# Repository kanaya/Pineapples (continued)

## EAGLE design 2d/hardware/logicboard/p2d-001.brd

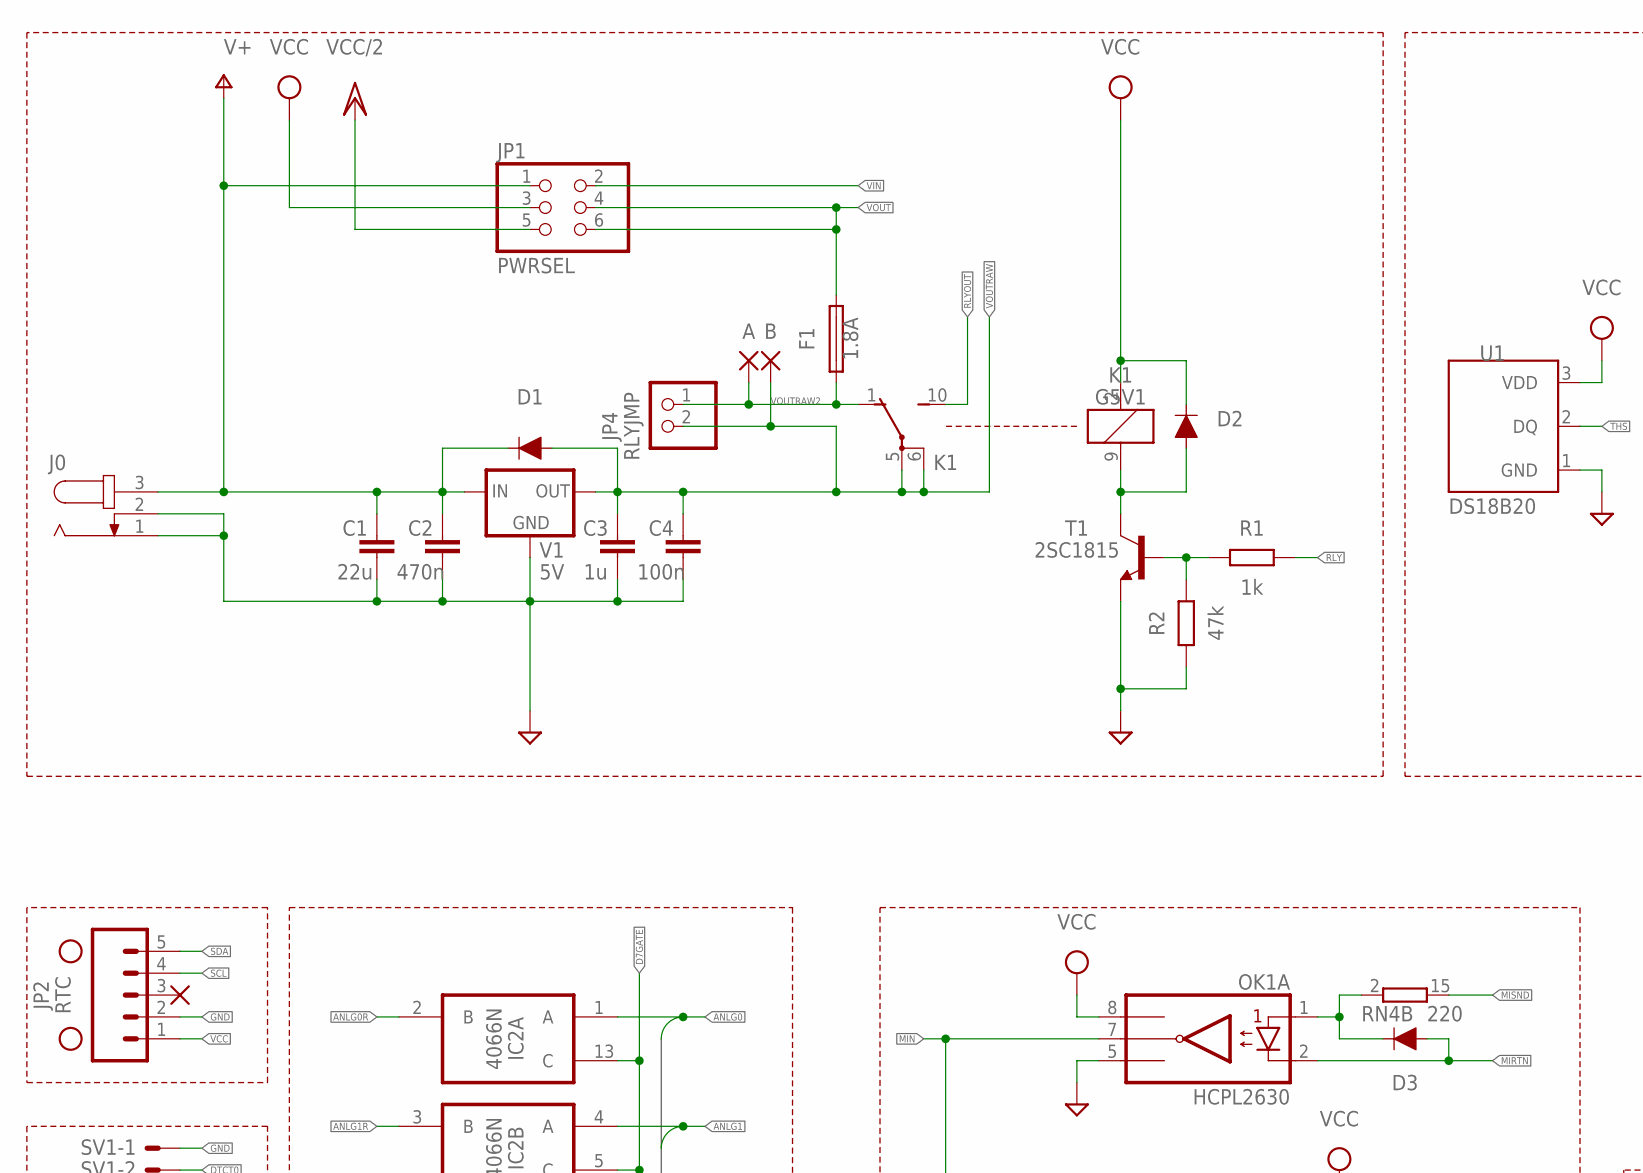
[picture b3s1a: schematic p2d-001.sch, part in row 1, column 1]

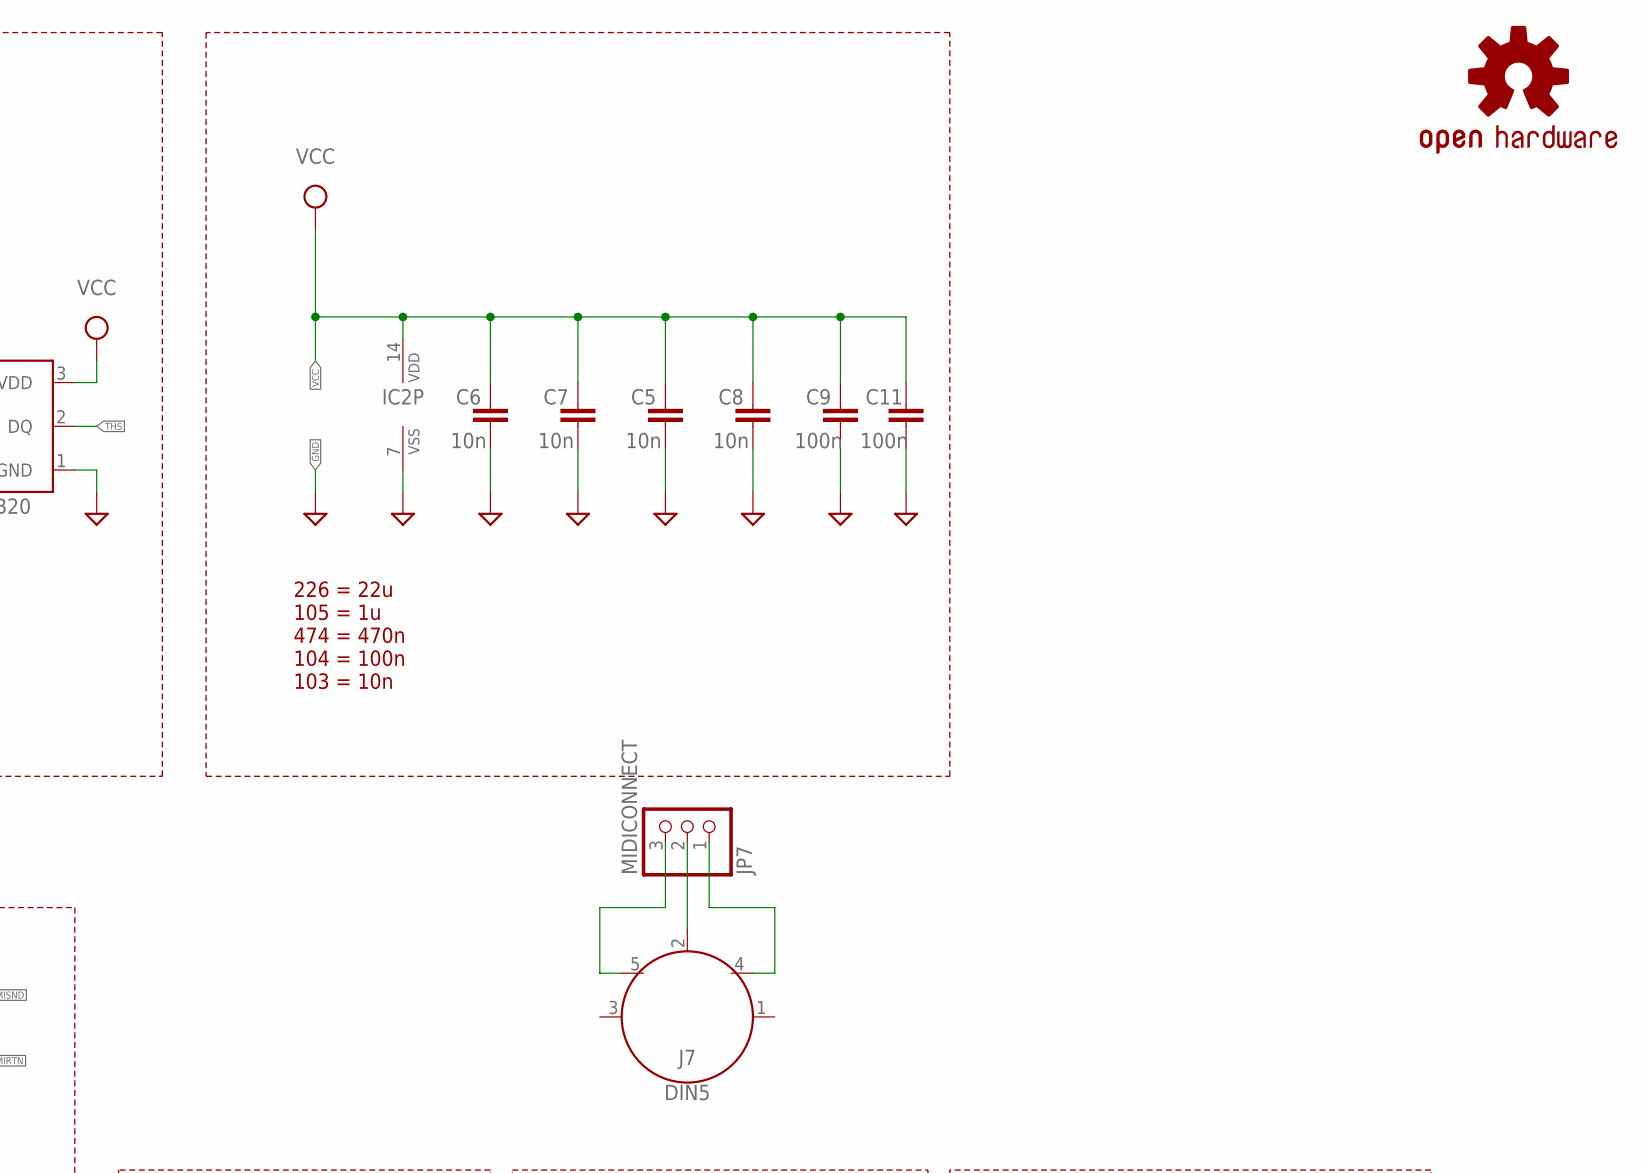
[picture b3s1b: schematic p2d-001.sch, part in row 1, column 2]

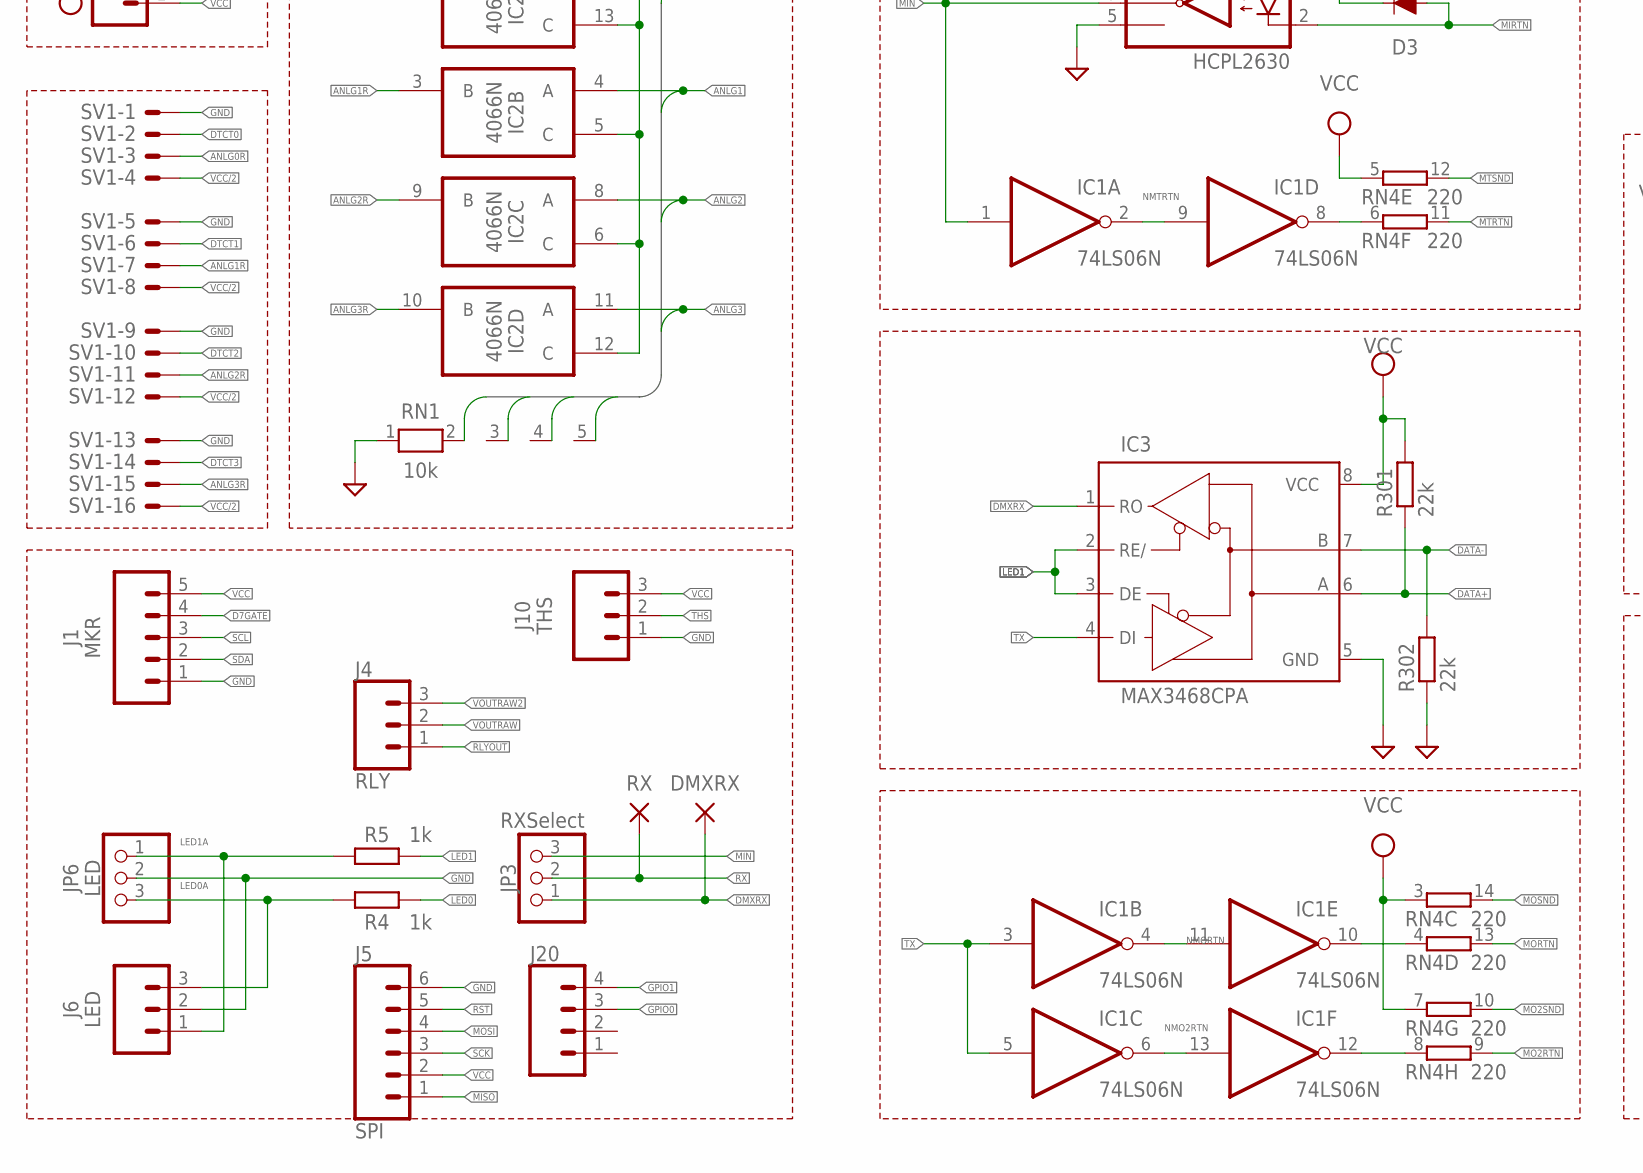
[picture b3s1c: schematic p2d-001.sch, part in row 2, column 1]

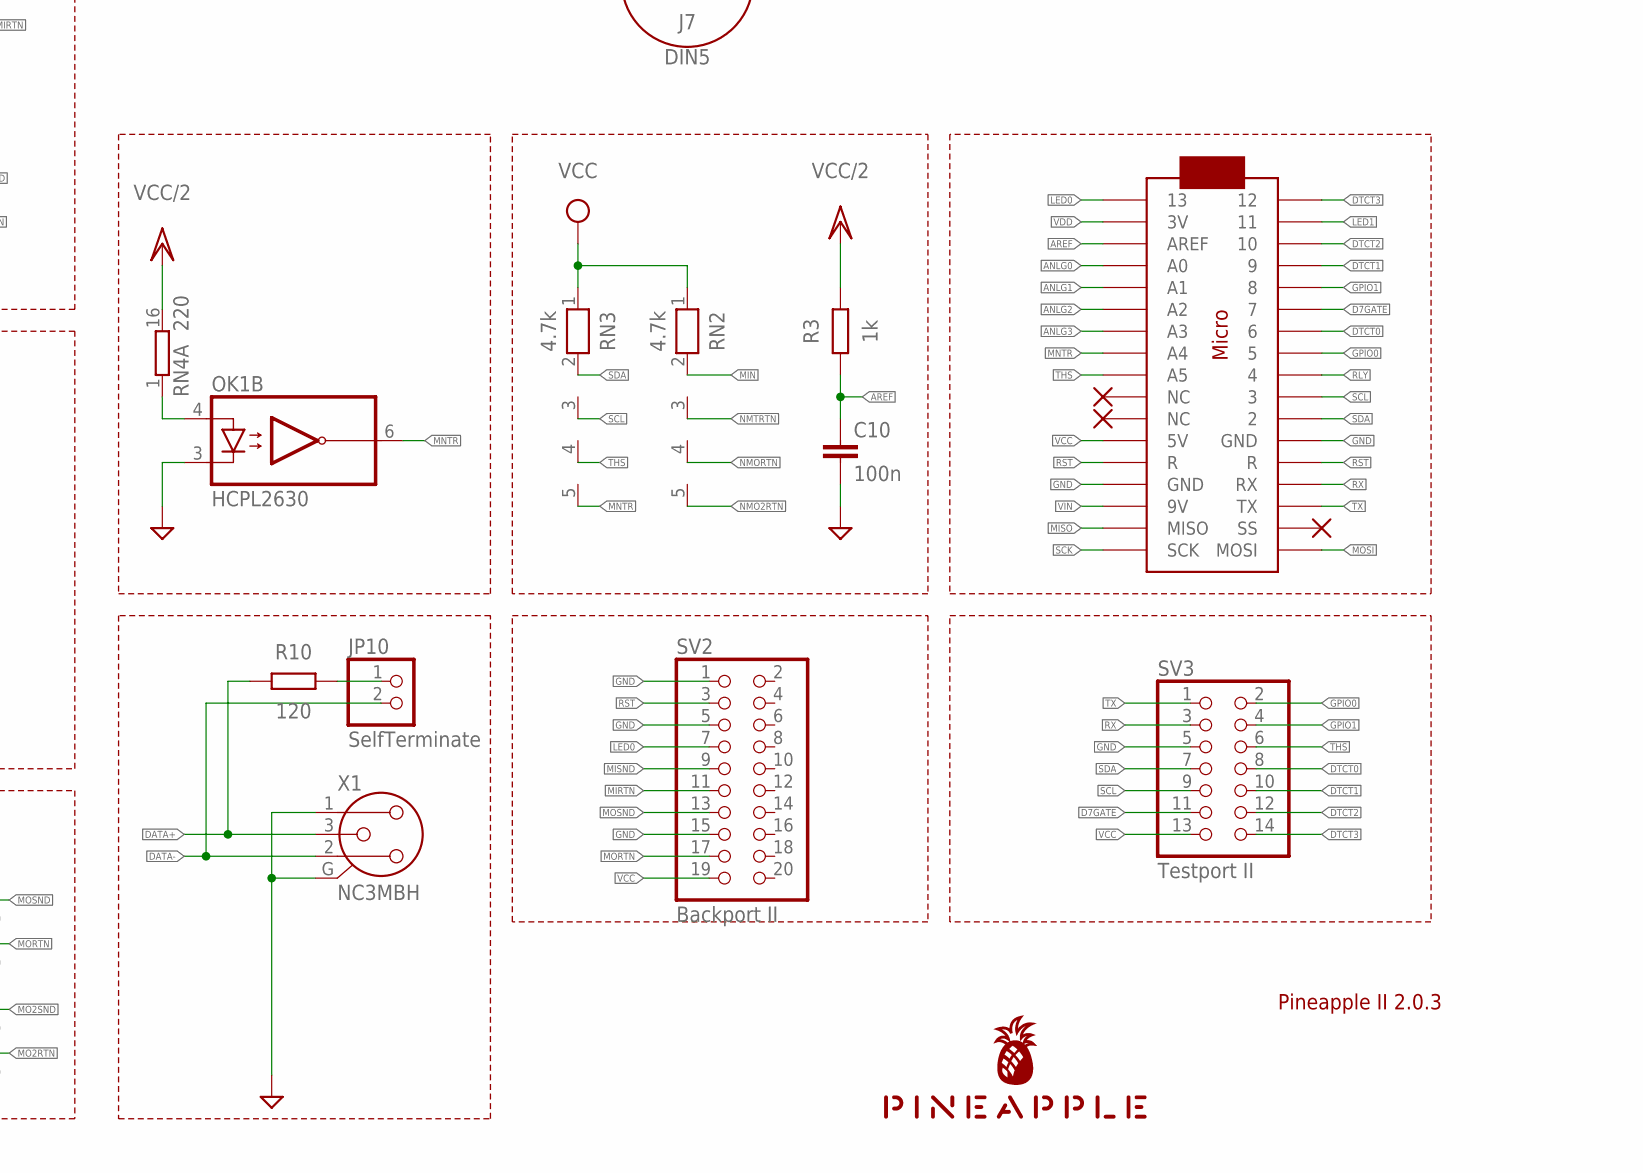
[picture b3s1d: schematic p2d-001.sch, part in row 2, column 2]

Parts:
A: SMD2; SMD1,27-2,54
B: SMD2; SMD1,27-2,54
C1: 22u; C025-050X050
C2: 470n; C050-024X044
C3: 1u; C050-024X044
C4, C9, C10, C11: 100n; C025-024X044
C5, C6, C7, C8: 10n; C025-024X044
D1, D2, D3: DIODE-1N4148
DMXRX: SMD2; SMD1,27-2,54
F1: 1.8A; TE5
H1, H2: STAND-OFF
IC1: 74LS06N; DIL14
IC2: 4066N; DIL14
IC3: MAX3468CPA; DIL08
J0: JACK-PLUG0; SPC4077
J1: MKR; JST-5-PTH
J4: RLY; JST-3-PTH-NS
J5: SPI; 1X06_1.27MM
J6: LED; JST-3-PTH-VERT
J7: DIN5; DIN5-RA-PTH
J10: THS; JST-3-PTH
J20: CONN_041.27MM; 1X04_1.27MM
JP1: PWRSEL; 2X03
JP2: RTC; 1X05
JP3: RXSelect; 1X03
JP4: RLYJMP; 1X02
JP6: LED; 1X03
JP7: MIDICONNECT; 1X03
JP10: SelfTerminate; 1X02
K1: G5V1
LOGO1: OSHW-LOGOS-COPPER; OSHW-LOGO-S_COPPER
MC1: ARDUINOMICRO
OK1: HCPL2630; DIL08
R1, R3, R4, R5: 1k; 0204/5
R2: 47k; 0204/5
R10: 120; 0204/5
R301, R302: 22k; M2012
RN1: 10k; RN-5
RN2, RN3: 4.7k; RN-5
RN4: 220; DIL16
RX: SMD2; SMD1,27-2,54
SV1: ML16LE; ML16L
SV2: Backport II; 2X10
SV3: Testport II; 2X07
T1: 2SC1815; TO92-ECB
U1: DS18B20; TO-92-AMMO
U$1: PINEAPPLE450_SILK
V1: 5V; 78XXL
X1: NC3MBH

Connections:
ANLG0: IC2.1 (A), MC1.P$31 (A0), RN1.2
ANLG0R: IC2.2 (B), SV1.3
ANLG1: IC2.4 (A), MC1.P$30 (A1), RN1.3
ANLG1R: IC2.3 (B), SV1.7
ANLG2: IC2.8 (A), MC1.P$29 (A2), RN1.4
ANLG2R: IC2.9 (B), SV1.11
ANLG3: IC2.11 (A), MC1.P$28 (A3), RN1.5
ANLG3R: IC2.10 (B), SV1.15
AREF: C10.1, MC1.P$32 (AREF), R3.1
D7GATE: IC2.5 (C), IC2.6 (C), IC2.12 (C), IC2.13 (C), J1.4, MC1.P$6 (7), SV3.11
DATA+: IC3.6 (A), R10.1, R301.1, X1.3
DATA+R: JP10.1, R10.2
DATA-: IC3.7 (B), JP10.2, R302.2, X1.2
DIN2: J7.2, JP7.2
DIN4: J7.4, JP7.1
DIN5: J7.5, JP7.3
DMXRX: DMXRX.1, IC3.1 (RO), JP3.1
DTCT0: MC1.P$7 (6), SV1.2, SV3.8
DTCT1: MC1.P$4 (9), SV1.6, SV3.10
DTCT2: MC1.P$3 (10), SV1.10, SV3.12
DTCT3: MC1.P$1 (12), SV1.14, SV3.14
GND: C1.2, C2.2, C3.2, C4.2, C5.2, C6.2, C7.2, C8.2, C9.2, C10.2, C11.2, IC1.7 (GND), IC2.7 (VSS), IC3.5 (GND), J0.1, J0.2, J1.1, J5.6, J6.2, J10.1, JP2.2, JP6.2, MC1.P$12 (GND), MC1.P$21 (GND), OK1.3 (C2), OK1.5 (GND), R2.1, R302.1, RN1.1, SV1.1, SV1.5, SV1.9, SV1.13, SV2.1, SV2.5, SV2.15, SV3.5, T1.E, U1.1 (GND), V1.GND, X1.1, X1.G
GPIO0: J20.3, MC1.P$8 (5), SV3.2
GPIO1: J20.4, MC1.P$5 (8), SV3.4
LED0: MC1.P$34 (13), R4.2, SV2.7
LED0A: J6.3, JP6.3, R4.1
LED1: IC3.2 (RE/), IC3.3 (DE), MC1.P$2 (11), R5.2
LED1A: J6.1, JP6.1, R5.1
MIN: IC1.1 (I), JP3.3, OK1.7 (VO1), RN2.2
MIRTN: D3.A, OK1.2 (C1), SV2.11
MISND: RN4.15 (2), SV2.9
MISNDA: D3.C, OK1.1 (A1), RN4.2 (1)
MISO: J5.1, MC1.P$19 (MISO)
MNTR: MC1.P$27 (A4), OK1.6 (VO2), RN3.5
MNTRA: OK1.4 (A2), RN4.1
MO2RTN: RN4.9 (2)
MO2RTNR: IC1.12 (O), RN4.8 (1)
MO2SND: RN4.10 (2)
MORTN: RN4.13 (2), SV2.17
MORTNR: IC1.10 (O), RN4.4 (1)
MOSI: J5.4, MC1.P$17 (MOSI)
MOSND: RN4.14 (2), SV2.13
MTRTN: RN4.11 (2)
MTRTNR: IC1.8 (O), RN4.6 (1)
MTSND: RN4.12 (2)
NMO2RTN: IC1.6 (O), IC1.13 (I), RN2.5
NMORTN: IC1.4 (O), IC1.11 (I), RN2.4
NMTRTN: IC1.2 (O), IC1.9 (I), RN2.3
RLY: MC1.P$9 (4), R1.2
RLYDRV: R1.1, R2.2, T1.B
RLYOUT: J4.1, K1.10 (S)
RLYSNK: D2.A, K1.9 (2), T1.C
RST: J5.5, MC1.P$13 (R), MC1.P$22 (R), SV2.3
RX: JP3.2, MC1.P$14 (RX), RX.1, SV3.3
SCK: J5.3, MC1.P$18 (SCK)
SCL: J1.3, JP2.4, MC1.P$10 (3), RN3.3, SV3.9
SDA: J1.2, JP2.5, MC1.P$11 (2), RN3.2, SV3.7
THS: J10.2, MC1.P$26 (A5), RN3.4, SV3.6, U1.2 (DQ)
TX: IC1.3 (I), IC1.5 (I), IC3.4 (DI), MC1.P$15 (TX), SV3.1
V+: C1.1, C2.1, D1.C, J0.3, JP1.1, V1.IN
VCC: C5.1, C6.1, C7.1, C8.1, C9.1, C11.1, D2.C, IC1.14 (VCC), IC2.14 (VDD), IC3.8 (VCC), J1.5, J5.2, J10.3, JP1.3, JP2.1, K1.2 (1), MC1.P$23 (5V), OK1.8 (VCC), R301.2, RN2.1, RN3.1, RN4.3 (1), RN4.5 (1), RN4.7 (1), SV2.19, SV3.13, U1.3 (VDD)
VCC/2: JP1.5, R3.2, RN4.16 (2), SV1.4, SV1.8, SV1.12, SV1.16
VDD: MC1.P$33 (3V)
VIN: JP1.2, MC1.P$20 (9V)
VOUT: F1.2, JP1.4, JP1.6
VOUTRAW: B.1, C3.1, C4.1, D1.A, J4.2, JP4.2, K1.5, K1.6, V1.OUT
VOUTRAW2: A.1, F1.1, J4.3, JP4.1, K1.1 (O)

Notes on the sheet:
Pineapple II 2.0.3
226 = 22u 105 = 1u 474 = 470n 104 = 100n 103 = 10n

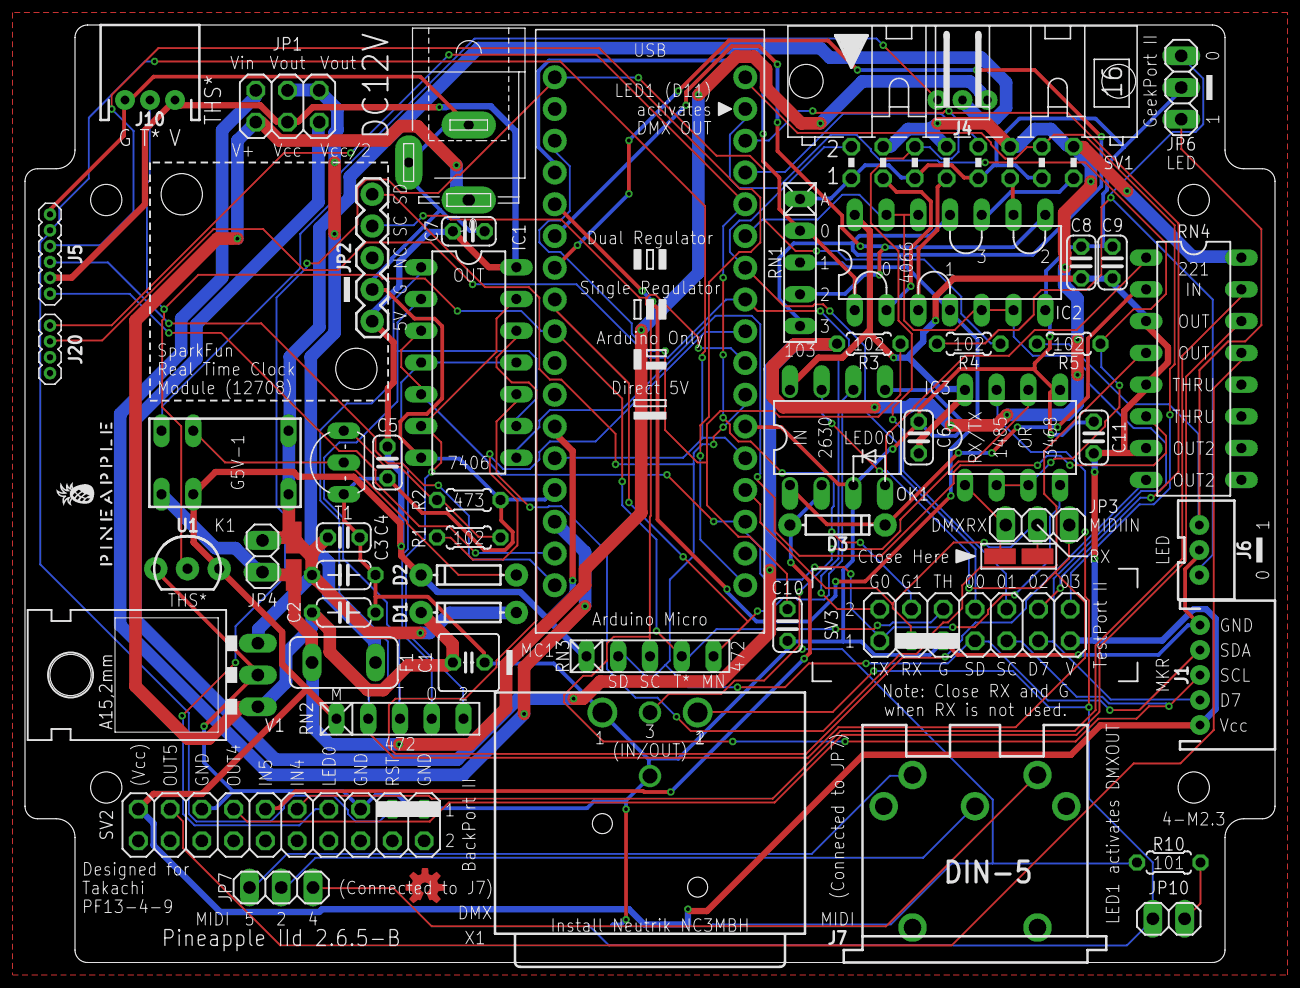
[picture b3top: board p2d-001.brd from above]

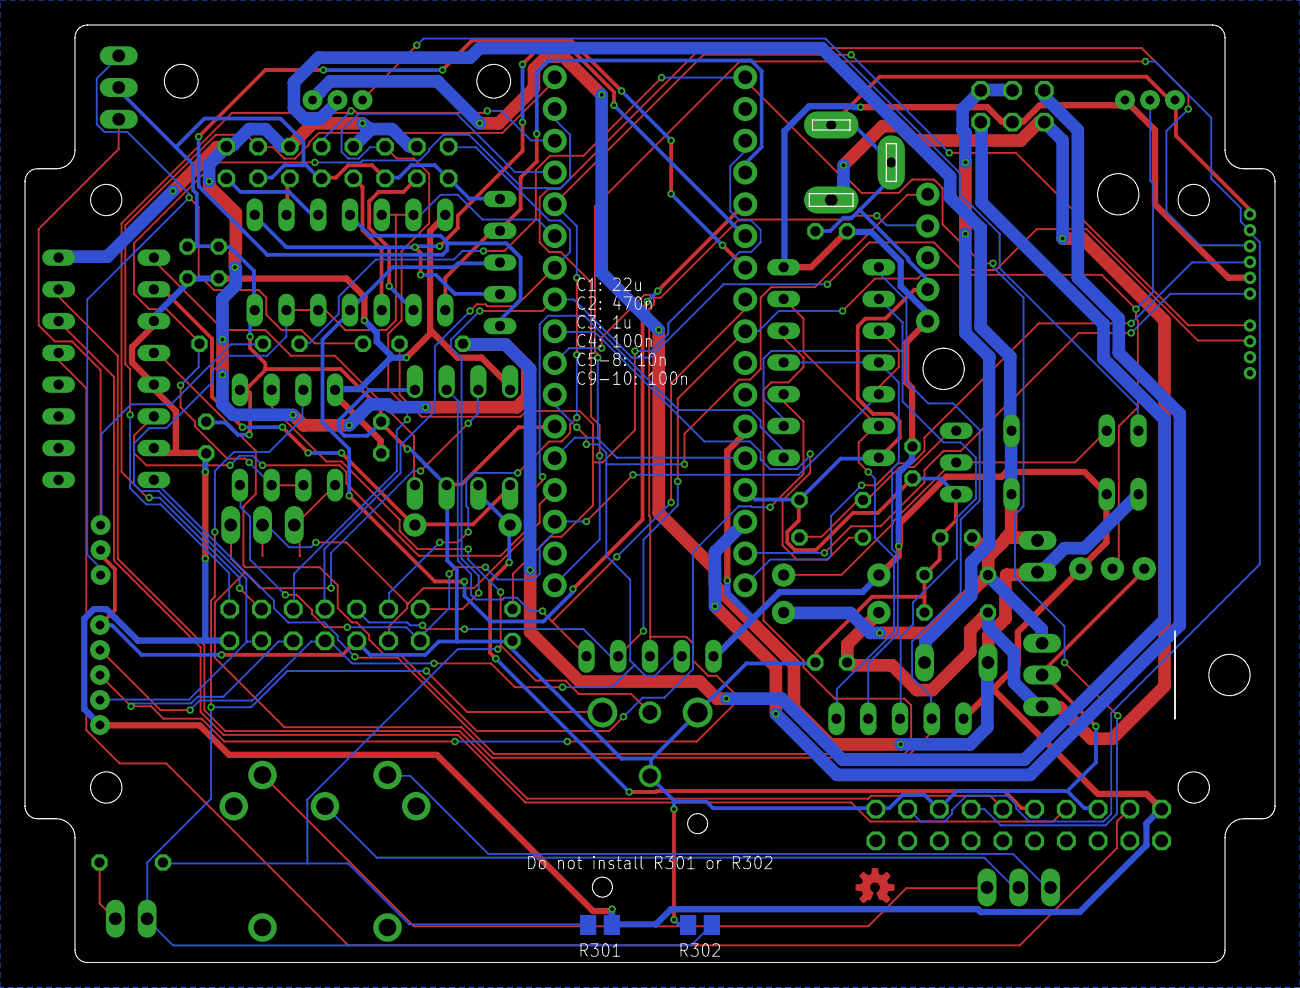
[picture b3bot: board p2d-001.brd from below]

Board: 2 copper layers, 100.0 x 75.0 mm, 63 parts (2 on the bottom side), 62 nets.

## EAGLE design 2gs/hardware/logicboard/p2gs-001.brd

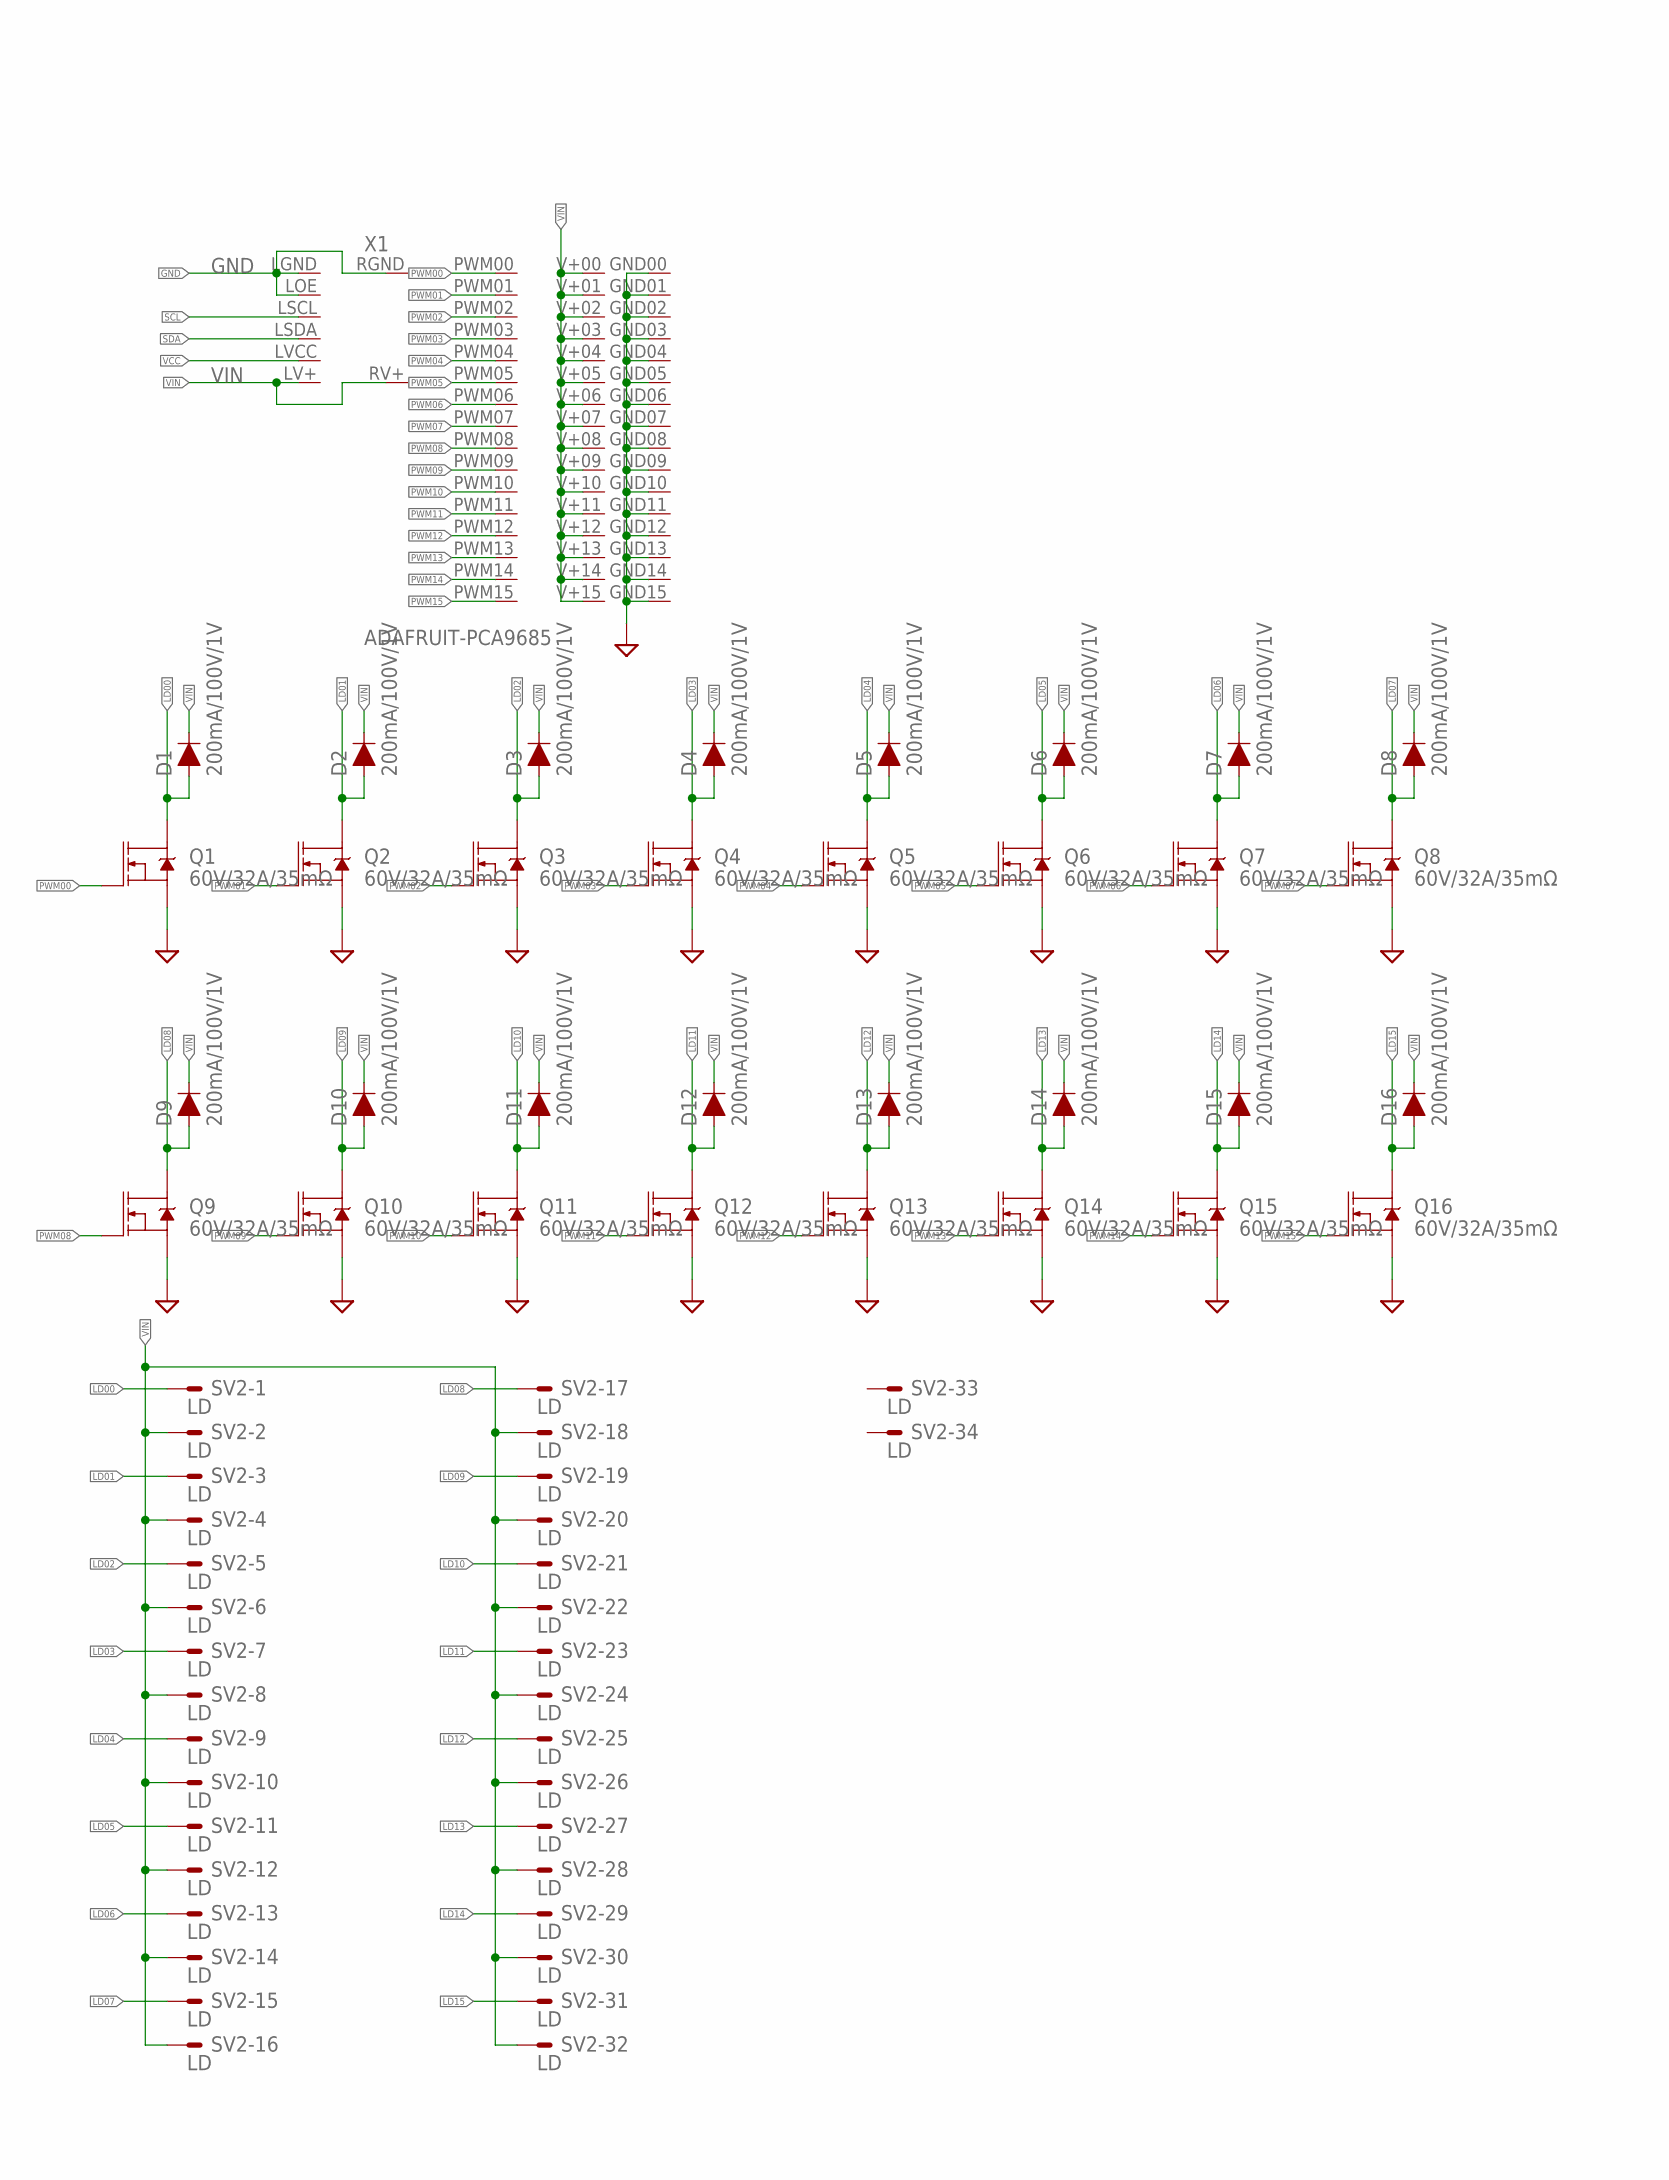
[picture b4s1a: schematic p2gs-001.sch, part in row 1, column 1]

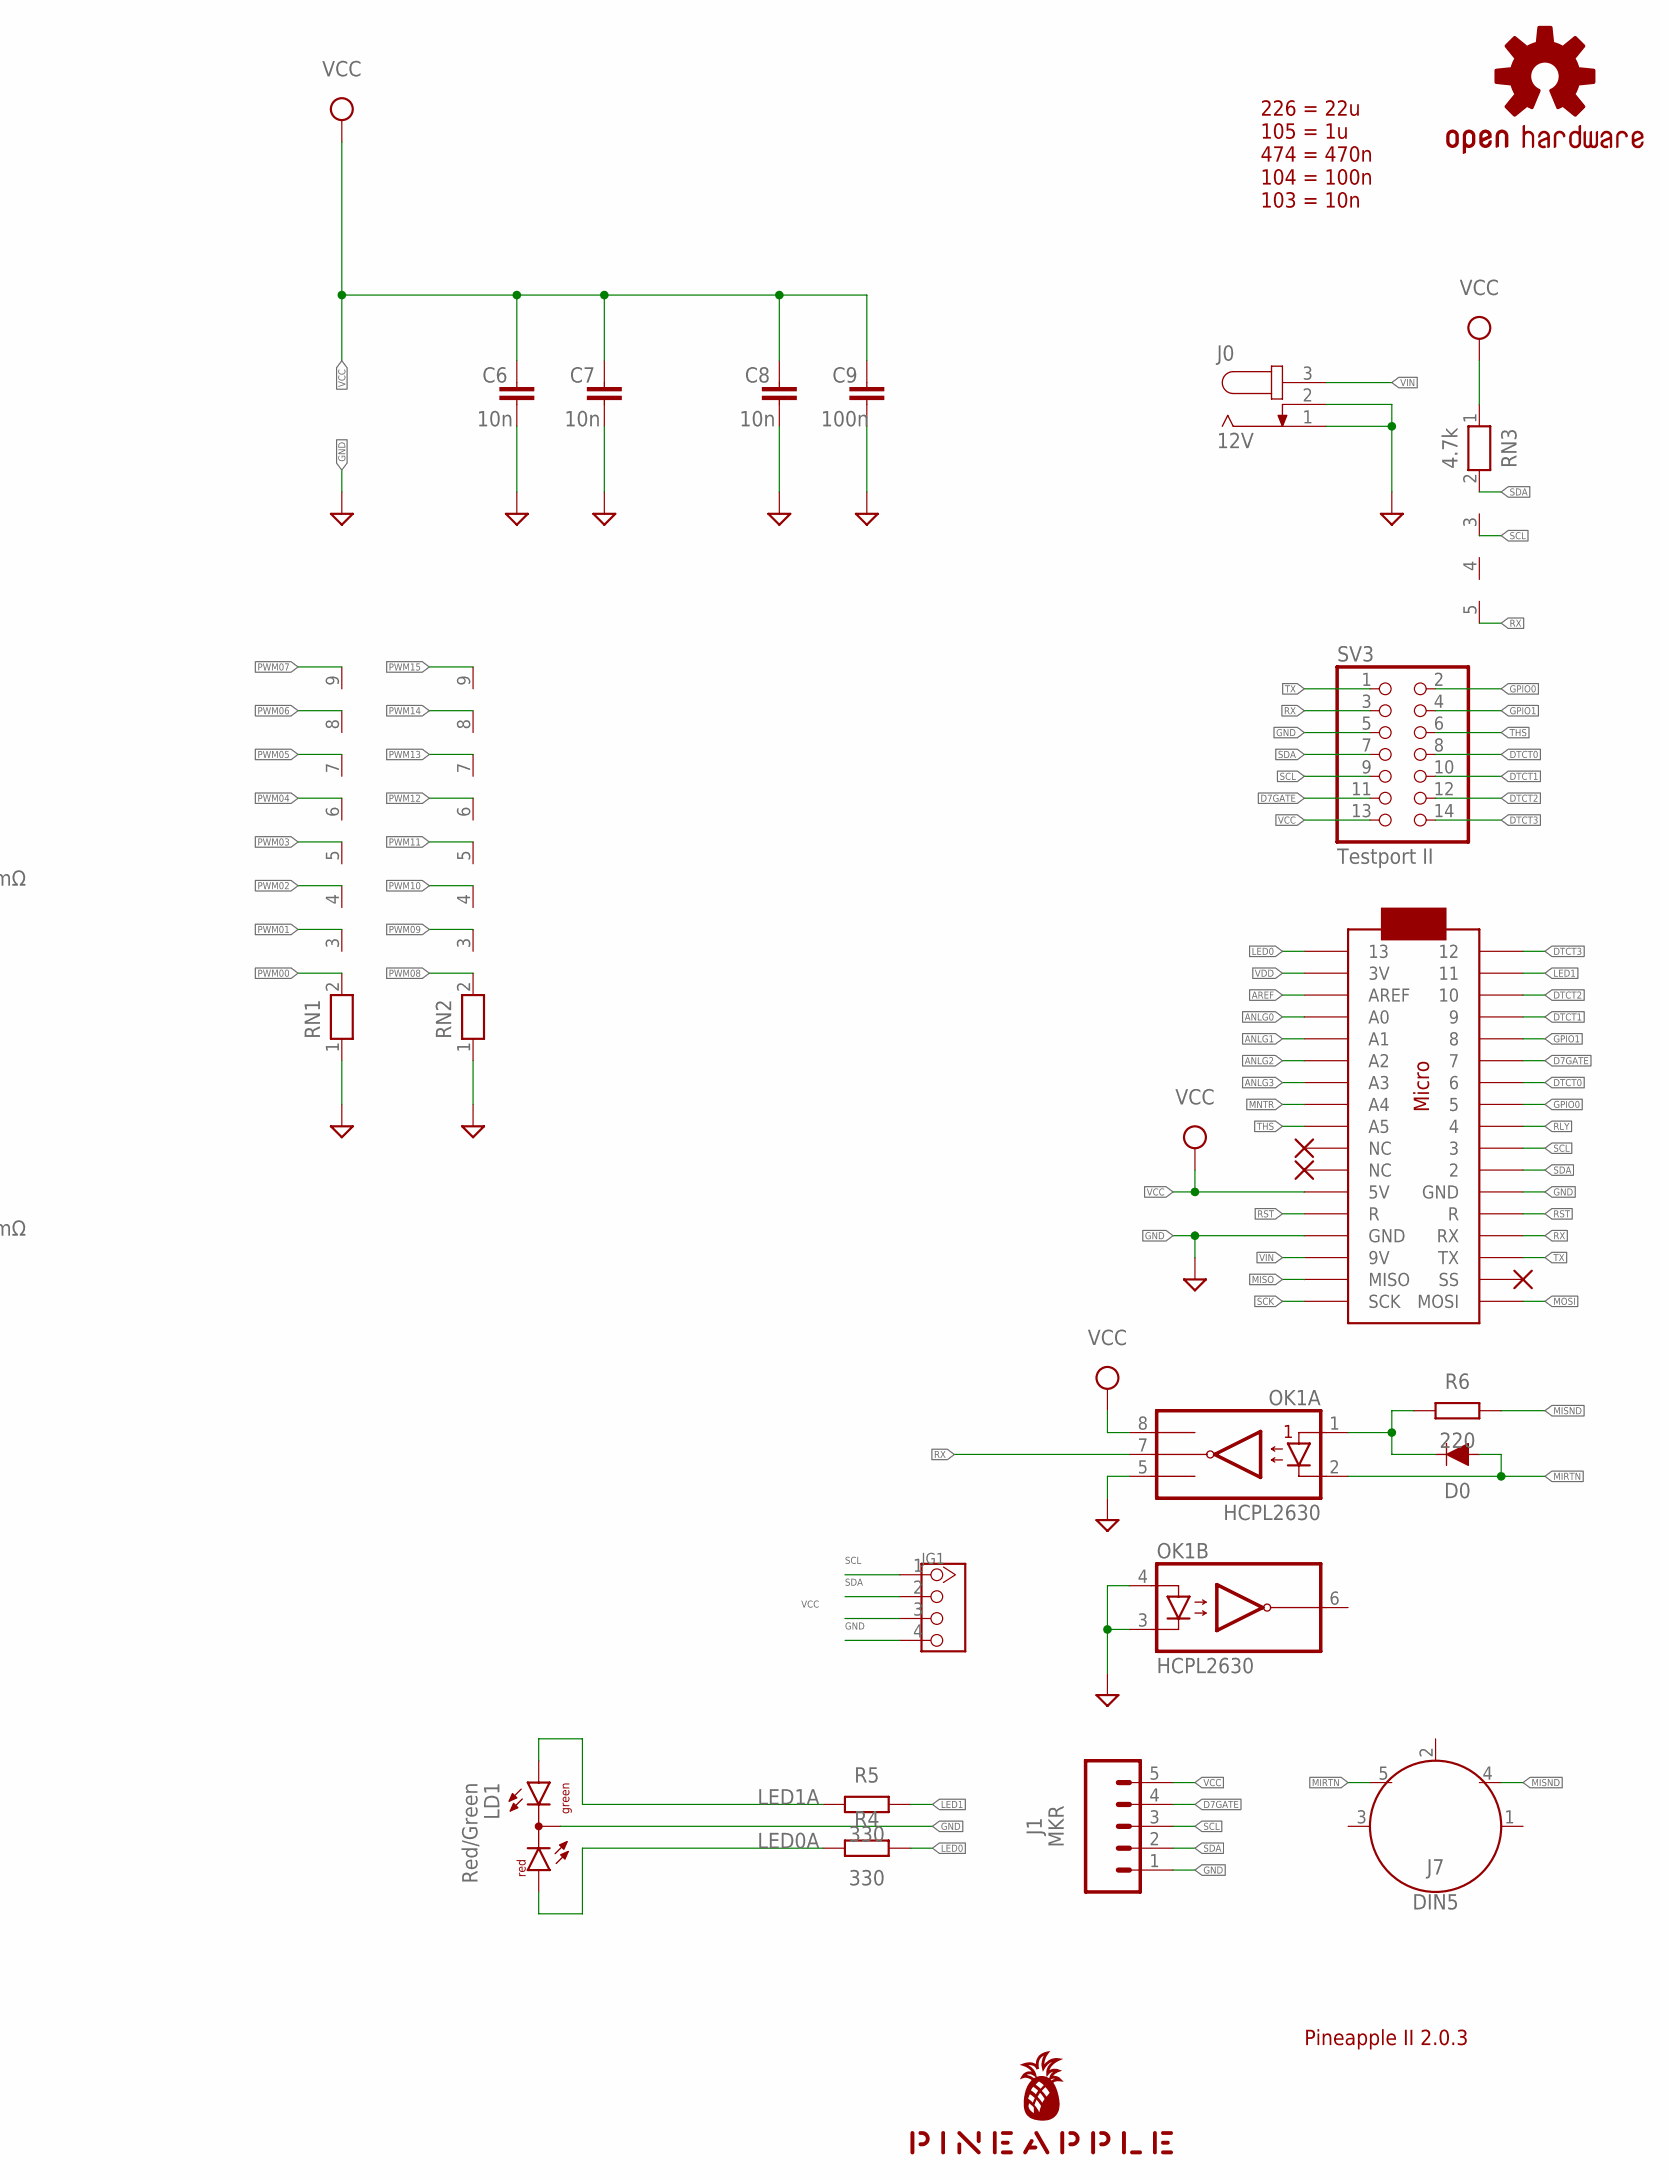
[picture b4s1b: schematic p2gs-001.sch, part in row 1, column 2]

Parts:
C6, C7, C8: 10n; C025-024X044
C9: 100n; C025-024X044
D0: DIODE-1N4148
D1, D2, D3, D4, D5, D6, D7, D8, D9, D10, D11, D12, D13, D14, D15, D16: 200mA/100V/1V; DIODE-1N4148
J0: 12V; SPC4077
J1: MKR; JST-5-PTH
J7: DIN5; DIN5-RA-PTH
JG1: TWIG-4P-2.0'90D'; 4P-2.0-90D
LD1: Red/Green; DUOLED-C-5MM
LOGO1: OSHW-LOGOS-COPPER; OSHW-LOGO-S_COPPER
MC1: ARDUINOMICRO
OK1: HCPL2630; DIL08
Q1, Q2, Q3, Q4, Q5, Q6, Q7, Q8, Q9, Q10, Q11, Q12, Q13, Q14, Q15, Q16: 60V/32A/35mΩ; TO220V
R4, R5: 330; 0204/5
R6: 220; 0204/5
RN1, RN2: RN08; RN-9
RN3: 4.7k; RN-5
SV2: LD; ML34L
SV3: Testport II; 2X07
U$1: PINEAPPLE450_SILK
X1: ADAFRUIT-PCA9685; ADAFRUIT-PCA9685-FOOTPRINT

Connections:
ANLG0: MC1.P$31 (A0)
ANLG1: MC1.P$30 (A1)
ANLG2: MC1.P$29 (A2)
ANLG3: MC1.P$28 (A3)
AREF: MC1.P$32 (AREF)
D7GATE: J1.4, MC1.P$6 (7), SV3.11
DTCT0: MC1.P$7 (6), SV3.8
DTCT1: MC1.P$4 (9), SV3.10
DTCT2: MC1.P$3 (10), SV3.12
DTCT3: MC1.P$1 (12), SV3.14
GND: C6.2, C7.2, C8.2, C9.2, J0.1, J0.2, J1.1, JG1.4, LD1.C, MC1.P$12 (GND), MC1.P$21 (GND), OK1.3 (C2), OK1.4 (A2), OK1.5 (GND), Q1.3 (S), Q2.3 (S), Q3.3 (S), Q4.3 (S), Q5.3 (S), Q6.3 (S), Q7.3 (S), Q8.3 (S), Q9.3 (S), Q10.3 (S), Q11.3 (S), Q12.3 (S), Q13.3 (S), Q14.3 (S), Q15.3 (S), Q16.3 (S), RN1.1, RN2.1, SV3.5, X1.GND00 (45), X1.GND01 (46), X1.GND02 (47), X1.GND03 (48), X1.GND04 (49), X1.GND05 (50), X1.GND06 (51), X1.GND07 (52), X1.GND08 (53), X1.GND09 (54), X1.GND10 (55), X1.GND11 (56), X1.GND12 (57), X1.GND13 (58), X1.GND14 (59), X1.GND15 (60), X1.LGND (1), X1.LOE (2), X1.RGND (7); also elsewhere on the board
GPIO0: MC1.P$8 (5), SV3.2
GPIO1: MC1.P$5 (8), SV3.4
LD00: D1.A, Q1.2 (D), SV2.1
LD01: D2.A, Q2.2 (D), SV2.3
LD02: D3.A, Q3.2 (D), SV2.5
LD03: D4.A, Q4.2 (D), SV2.7
LD04: D5.A, Q5.2 (D), SV2.9
LD05: D6.A, Q6.2 (D), SV2.11
LD06: D7.A, Q7.2 (D), SV2.13
LD07: D8.A, Q8.2 (D), SV2.15
LD08: D9.A, Q9.2 (D), SV2.17
LD09: D10.A, Q10.2 (D), SV2.19
LD10: D11.A, Q11.2 (D), SV2.21
LD11: D12.A, Q12.2 (D), SV2.23
LD12: D13.A, Q13.2 (D), SV2.25
LD13: D14.A, Q14.2 (D), SV2.27
LD14: D15.A, Q15.2 (D), SV2.29
LD15: D16.A, Q16.2 (D), SV2.31
LED0: MC1.P$34 (13), R4.2
LED0A: LD1.AR, R4.1
LED1: MC1.P$2 (11), R5.2
LED1A: LD1.AX (AG), R5.1
MIDIINSND: D0.C, OK1.1 (A1), R6.1
MIRTN: D0.A, J7.5, OK1.2 (C1)
MISND: J7.4, R6.2
MISO: MC1.P$19 (MISO)
MNTR: MC1.P$27 (A4)
MOSI: MC1.P$17 (MOSI)
PWM00: Q1.1 (G), RN1.2, X1.PWM00 (13)
PWM01: Q2.1 (G), RN1.3, X1.PWM01 (14)
PWM02: Q3.1 (G), RN1.4, X1.PWM02 (15)
PWM03: Q4.1 (G), RN1.5, X1.PWM03 (16)
PWM04: Q5.1 (G), RN1.6, X1.PWM04 (17)
PWM05: Q6.1 (G), RN1.7, X1.PWM05 (18)
PWM06: Q7.1 (G), RN1.8, X1.PWM06 (19)
PWM07: Q8.1 (G), RN1.9, X1.PWM07 (20)
PWM08: Q9.1 (G), RN2.2, X1.PWM08 (21)
PWM09: Q10.1 (G), RN2.3, X1.PWM09 (22)
PWM10: Q11.1 (G), RN2.4, X1.PWM10 (23)
PWM11: Q12.1 (G), RN2.5, X1.PWM11 (24)
PWM12: Q13.1 (G), RN2.6, X1.PWM12 (25)
PWM13: Q14.1 (G), RN2.7, X1.PWM13 (26)
PWM14: Q15.1 (G), RN2.8, X1.PWM14 (27)
PWM15: Q16.1 (G), RN2.9, X1.PWM15 (28)
RLY: MC1.P$9 (4)
RST: MC1.P$13 (R), MC1.P$22 (R)
RX: MC1.P$14 (RX), OK1.7 (VO1), RN3.5, SV3.3
SCK: MC1.P$18 (SCK)
SCL: J1.3, JG1.1, MC1.P$10 (3), RN3.3, SV3.9, X1.LSCL (3); also elsewhere on the board
SDA: J1.2, JG1.2, MC1.P$11 (2), RN3.2, SV3.7, X1.LSDA (4); also elsewhere on the board
THS: MC1.P$26 (A5), SV3.6
TX: MC1.P$15 (TX), SV3.1
VCC: C6.1, C7.1, C8.1, C9.1, J1.5, JG1.3, MC1.P$23 (5V), OK1.8 (VCC), RN3.1, SV3.13, X1.LVCC (5); also elsewhere on the board
VDD: MC1.P$33 (3V)
VIN: D1.C, D2.C, D3.C, D4.C, D5.C, D6.C, D7.C, D8.C, D9.C, D10.C, D11.C, D12.C, D13.C, D14.C, D15.C, D16.C, J0.3, MC1.P$20 (9V), SV2.2, SV2.4, SV2.6, SV2.8, SV2.10, SV2.12, SV2.14, SV2.16, SV2.18, SV2.20, SV2.22, SV2.24, SV2.26, SV2.28, SV2.30, SV2.32, X1.LV+ (6), X1.RV+ (12), X1.V+00 (29), X1.V+01 (30), X1.V+02 (31), X1.V+03 (32), X1.V+04 (33), X1.V+05 (34), X1.V+06 (35), X1.V+07 (36), X1.V+08 (37), X1.V+09 (38), X1.V+10 (39), X1.V+11 (40), X1.V+12 (41), X1.V+13 (42), X1.V+14 (43), X1.V+15 (44)

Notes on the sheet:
Pineapple II 2.0.3
226 = 22u 105 = 1u 474 = 470n 104 = 100n 103 = 10n
